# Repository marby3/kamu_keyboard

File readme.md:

# Kamu Keyboard 

Kamu Keyboardは分割型の10%カラム・スタッガードキーボードです。  
キーボードを組み立てるために必要な部品は以下の通りです。  

- PCB   x1  
- ProMicro  x2  
- TRRSジャック  x2  
- タクトスイッチ    x2  
- スイッチソケット（Cherry MX） x10  
- OLED（オプション）    x2  
- アクリルプレート 2mm（トップ）    x2
- アクリルプレート 2mm（ボトム）    x2
- アクリルプレート 2mm（カバー）    x2
- M2 ネジ（皿ねじ以外で3mm以上5mm以下で）   x28
- M2 スペーサー 7mm x14

PCBは[kamu_keyboard_pcb]>[gerber]内にあるファイルをJLCPCBやElecrowなどで発注することで注文が可能です。（ZIPファイルがあるのでそれを利用すると良いです）  

アクリルプレートは[kamu_keyboard_pcb]>[Plate_data]内にあるファイルを遊舎工房やElecrowなどのアクリルカットサービスが可能な業者にて加工をお願いしてください。  
1つのファイルで1セット分が加工できるようにファイルを用意しています。  

組み立て手順は[Kamu Keyboardの組み立て方](/build_guide/buildguide.md)をご覧ください。

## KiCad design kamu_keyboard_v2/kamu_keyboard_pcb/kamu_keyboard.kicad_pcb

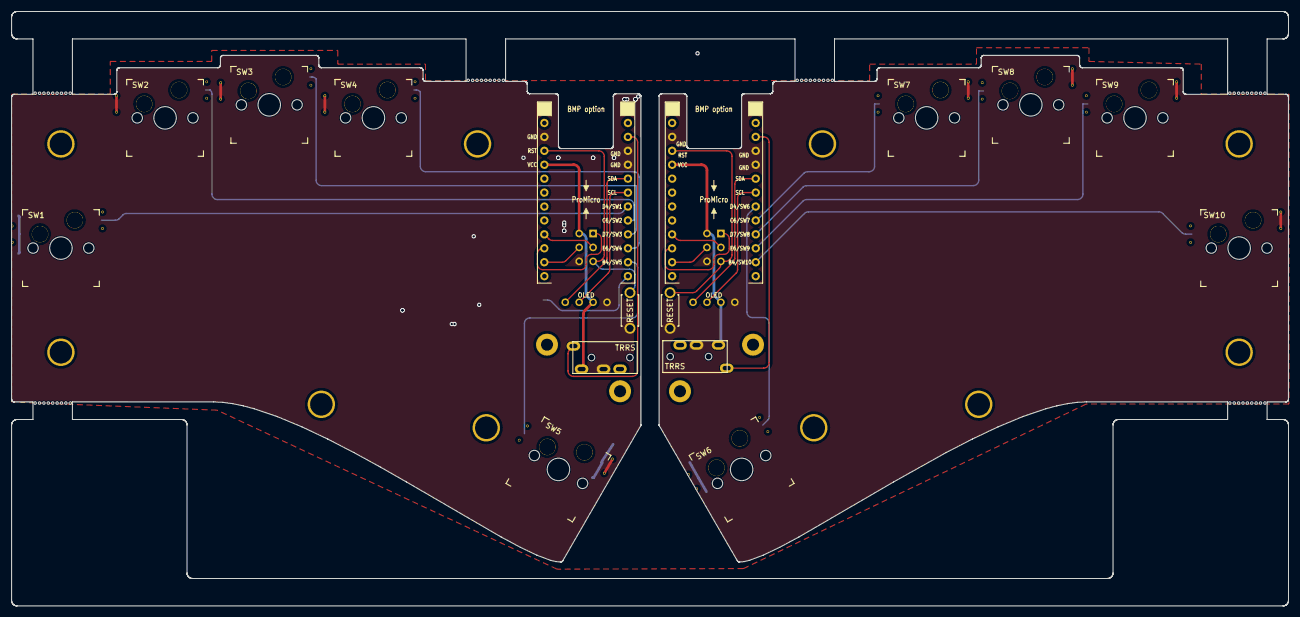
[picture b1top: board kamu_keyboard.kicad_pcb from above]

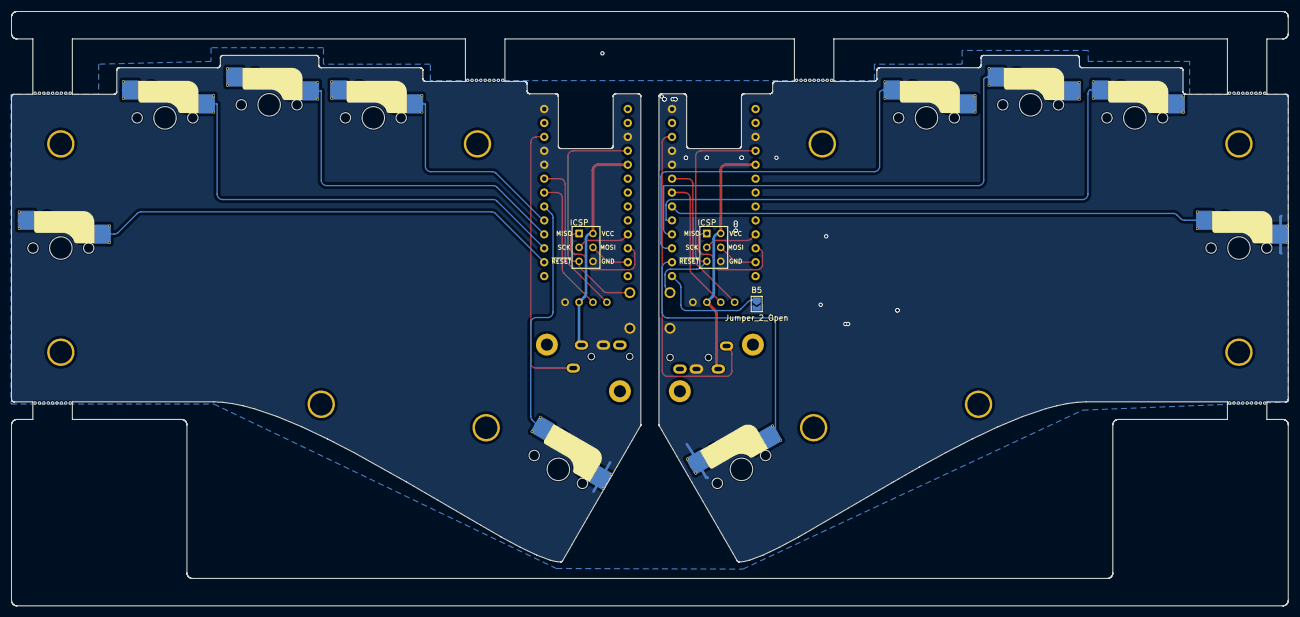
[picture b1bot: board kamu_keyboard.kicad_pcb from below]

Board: 2 copper layers, 232.9 x 108.4 mm, 21 parts (13 on the bottom side), 27 nets.

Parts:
J1, J3: OLED
J2, J4: ICSP
J5, J6: TRRS; MJ-4PP-9_1side
JP1: Jumper_2_Open; SolderJumper-2_P1.3mm_Open_TrianglePad1.0x1.5mm
RSW1, RSW2: SW_PUSH; ResetSW_1side
SW1, SW2, SW3, SW4, SW5, SW6, SW7, SW8, SW9, SW10: SW_PUSH; CherryMXSwitch_hotswap_1_00u
U1, U2: ProMicro; Board_BMP_Flip_Side

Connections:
/L_Data: J5.S, U1.2 (RX1/D2)
/L_MISO: J2.1, U1.15 (B3/14)
/L_MOSI: J2.4, U1.14 (B2/16)
/L_RST: J2.5, RSW1.2, U1.22 (RST)
/L_SCL: J1.2 (SCL), U1.6 (3/D0/SCL)
/L_SCLK: J2.3, U1.16 (B1/15)
/L_SDA: J1.1 (SDA), U1.5 (2/D1/SDA)
/L_push1: SW1.2, U1.7 (4/D4)
/L_push2: SW2.2, U1.8 (5/C6)
/L_push3: SW3.2, U1.9 (6/D7)
/L_push4: SW4.2, U1.10 (7/E6)
/L_push5: SW5.1, U1.11 (8/B4)
/L_side: JP1.1 (A), U1.12 (9/B5)
/R_Data: J6.S, U2.2 (RX1/D2)
/R_MISO: J4.1, U2.15 (B3/14)
/R_MOSI: J4.4, U2.14 (B2/16)
/R_RST: J4.5, RSW2.1, U2.22 (RST)
/R_SCL: J3.2 (SCL), U2.6 (3/D0/SCL)
/R_SCLK: J4.3, U2.16 (B1/15)
/R_SDA: J3.1 (SDA), U2.5 (2/D1/SDA)
/R_push6: SW6.2, U2.7 (4/D4)
/R_push7: SW7.1, U2.8 (5/C6)
/R_push8: SW8.1, U2.9 (6/D7)
/R_push9: SW9.1, U2.10 (7/E6)
/R_push10: SW10.1, U2.11 (8/B4)
GND: J1.4 (GND), J2.6, J3.4 (GND), J4.6, J5.R1, J6.R1, JP1.2 (B), RSW1.1, RSW2.2, SW1.1, SW2.1, SW3.1, SW4.1, SW5.2, SW6.1, SW7.2, SW8.2, SW9.2, SW10.2, U1.3 (GND), U1.4 (GND), U1.23 (GND), U1.26 (Bat-), U2.3 (GND), U2.4 (GND), U2.23 (GND), U2.26 (Bat-)
VCC: J1.3 (VCC), J2.2, J3.3 (VCC), J4.2, J5.T, J6.T, U1.21 (VCC), U2.21 (VCC)

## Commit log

2023-12-06 データ追加
2024-02-18 トッププレート&ボトムプレートにPCBデザインを追加
2024-02-24 fix_gerber
2024-02-24 fix gerber
2024-02-24 fix Acrylic data
